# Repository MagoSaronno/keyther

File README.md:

# Keyther Keyboard
The Keyther Keyboard represents an attempt at perfecting the already great [Cantor Classic](https://github.com/diepala/cantor "The original project").  The name comes from the combination of the substantives **Keyboard** and **Ethernet**, due to the use of an RJ45 socket. 

*Special thanks to both [diepala](https://github.com/diepala "The Cantor Keyboard creator") and [daprice](https://github.com/daprice "The creator of the footprints libraries") for having paved the way for the creation of the Keyther Keyboard.*

### What changes from Cantor

1. The TRRS socket is replaced with the more secure RJ45 (Ethernet) to avoid *critical* integrity issues caused by accidental disconnection or hot-plugging.  Indeed, the Keyther Keyboard supports hot-plugging, as shown in this video:
 <p align="center"> 
   
</p>

2. The design introduces **hot-swappable** Kailh Choc **sockets** and **handedness by pin** (through the addition of a 10k resistor and an added line in the config.h file)
You won't have to desolder all 42 switches to change them and you will be able to connect the keyboard even through the right half.

3. The horizontal space between switches has been *increased*, accommodating larger hands **without** additional modifications to the overall PCB size (expept the space for the RJ45 socket).

### What does not change

The keyther keyboard keeps (*for the most part*) the original concepts that were at the origin of Cantor, which are the diodeless design and the use of an invertible PCB design, to ultimately avoid cuttable costs.

### Why RJ45 instead of USB-C or magnetic pogo pin sockets?

The main reasons to use RJ45 sockets are their easy soldering, their overall diffusion, and the widespread presence of premade cables of different kinds, like coiled, straight, and flat.

Additionally, the number of pins present on the socket allows the possible addition of two optional communication lines between PCBs for whatever use (namely pins 1 and 5).

# Be Aware
The Keyther Keyboard is designed to be used with ***STRAIGHT-THROUGH CABLES***, not the crossover ones.

***Always check the cable type before connecting the two halves***.

## Disclaimer
All the designs and files are provided "AS IS" without any warranty or support.

## Links Index

[Ordering Guide](docs/Ordering_Guide.md)

[Assembly Guide](docs/Assembling_Guide.md)

[Firmware Guide](https://qmk.fm/guide "The default guide for the Cantor Keyboard")

## Quick Guide

### Bill of Materials (BOM)
The required components needed to assemble the keyboard are the following:
| N. | Item                                                                                                                                        | Notes                                                                  |
|----|---------------------------------------------------------------------------------------------------------------------------------------------|------------------------------------------------------------------------|
| 2  | PCB board                                                                                                                                   |                                                                        |
| 2  | STM32F401CC BlackPill microcontrollers                                                                                                      | *on [AliExpress](https://it.aliexpress.com/item/1005005953179540.html?)* |
| 4  | 20 pin stripes                                                                                                                              | *usually included with the Blackpill*                                  |
| 42 | Kailh Choc ***v1*** switches                                                                                                                | *namely the Kailh PG1350*                                                |
| 42 | Kailh Choc hot-swap sockets                                                                                                                 |                                                                        |
| 42 | Kailh Choc ***v1*** compatible keycaps                                                                                                      |                                                                        |
| 2  | RJ45 sockets (RJHSE type, e.g., the [RJHSE-XM80](https://docs.rs-online.com/b456/A700000007566767.pdf "The technical drawing of the socket"))| *on [AliExpress](https://it.aliexpress.com/item/1005007661898327.html?)* |
| 1  | Straight-through Ethernet cable                                                                                                             | *flat ones seem to be more flexible and less annoying when using the keyboard*     |
| 1  | USB-C cable compatible with your computer                                                                                                   |                                                                        |

### Ordering the PCB
To order the PCB, you will need the Gerber files present in the [Release section](https://github.com/MagoSaronno/keyther/releases). Then, you can either compare the prices on [PCBShopper](https://pcbshopper.com/ "A price comparison site for printed PCBs") by choosing a dimension of 150x90mm or upload them directly to the PCB manufacturer's website of choice.

You can refer to the [Ordering Tutorial](docs/Ordering_Guide.md) page which provides a step-by-step guide on the ordering procedure.

> I personally prototyped my PCBs using JLCPCB, primarily due to lower prices. However, these may vary depending on your customs policies and regional shipping rates.

### Firmware
> It is preferable to flash and check the microcontroller for defects before assembling the keyboard.

The Keyther Keyboard uses the [QMK Firmware](https://qmk.fm/), specifically the same as the Cantor Keyboard. You can easily follow the [guide](https://qmk.fm/guide "The default guide for the Cantor Keyboard") on the QMK website to *customise* and *compile* the firmware.

To add **language-specific characters** (such as *accented* or *umlaut* vowels) you can follow this [additional guide](Language-Specific_Keymap.md).

Unfortunately, at this time, to add the handedness feature to your keyboard you will need to use the [QMK source](https://docs.qmk.fm/newbs "The guide to use the source"), and, before compiling, add to the cantor's config.h file the line:

`#define SPLIT_HAND_PIN B12`

### Enter Bootloader Mode
To flash the firmware onto the microcontroller you will need to set it in bootloader mode first:
- Press and hold the BOOT0 button.
- Press and release the NRST button.
- Release the BOOT0 button.

Now you will be able to flash the firmware and check if the microcontroller works properly.

> Once the first flash has been done successfully you will be able to enter bootloader mode just by plugging in one half of the keyboard **while** holding down the top-left or top-right (*whether it is the left or right keyboard half*).

### Assemble the keyboard
To assemble your Keyther Keyboard you will need a soldering iron and tin of your choice. You can also follow the [Assembly Guide](docs/Assembling_Guide.md).

### Printing the Keyther cases
To 3D print the cases to protect the bottom of your keyboard halves you will need to download the *.stl* files present in the [case folder](https://github.com/MagoSaronno/keyther/tree/main/case) of this repository and slice them with the appropriate software.

In case you wish to modify the designs, you can download the *.step* files in the [step folder](https://github.com/MagoSaronno/keyther/tree/main/case/step).
I've personally succeded in printing them using generic PLA with a layer height of 0.2mm and no supports.

## Feedback
You can fill out [this form](https://forms.gle/tCP48DNiQqiqbWwy6 "Leave here your much appreciated feedback") to let me know of any potential improvements or issues with the project. 

### Have fun!

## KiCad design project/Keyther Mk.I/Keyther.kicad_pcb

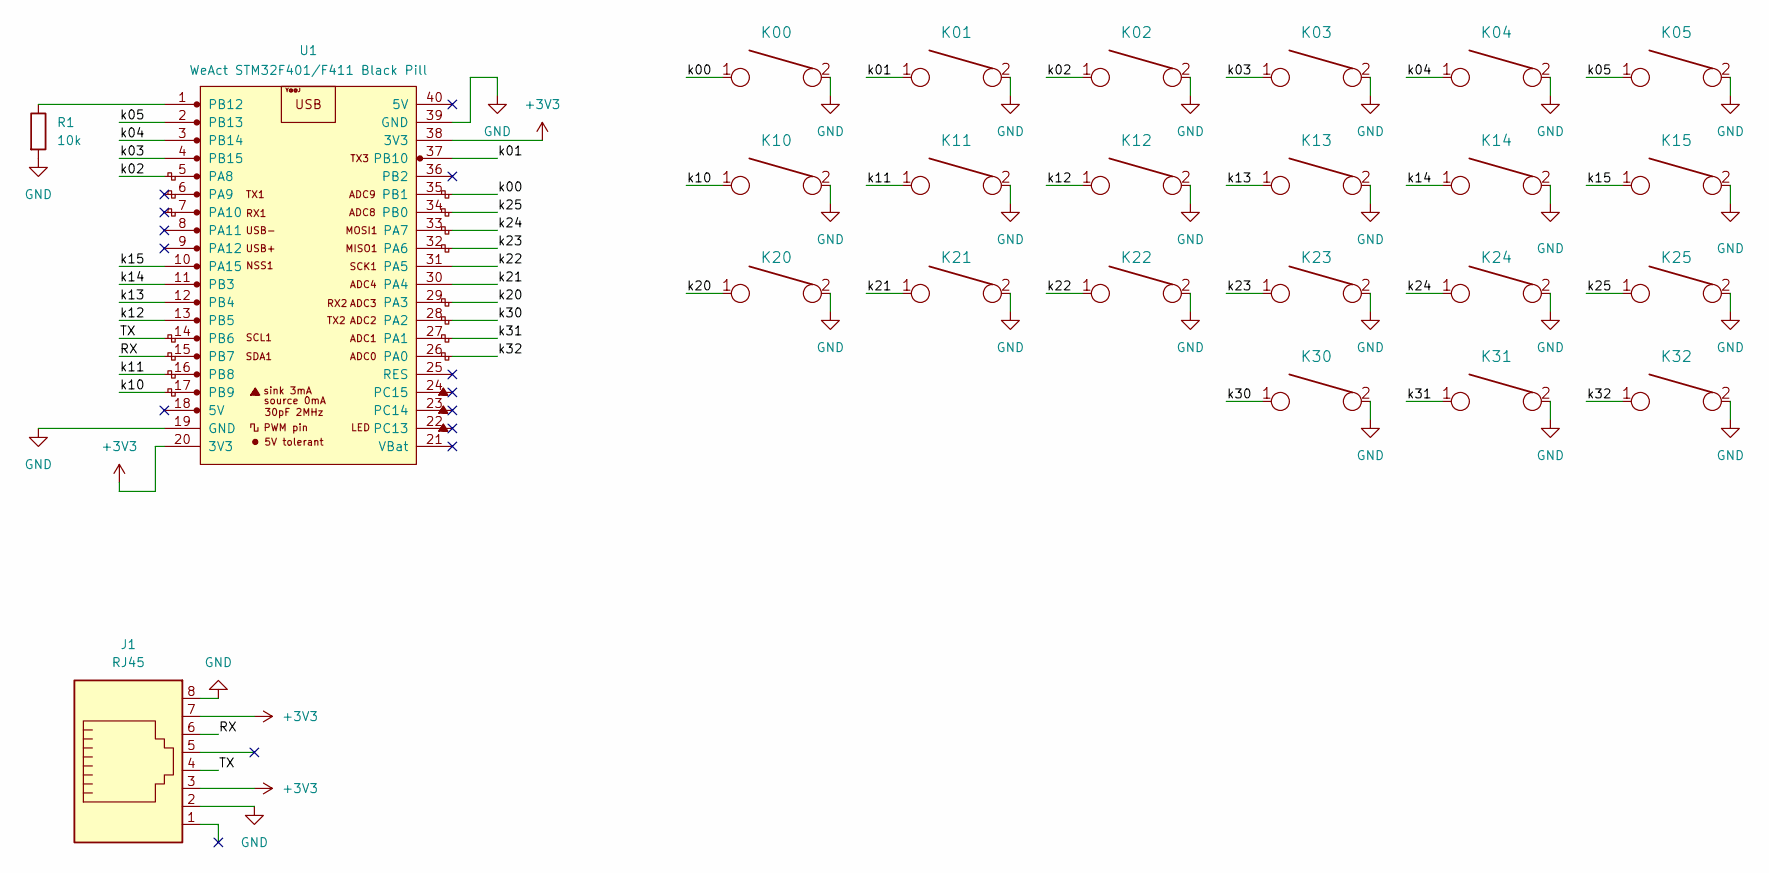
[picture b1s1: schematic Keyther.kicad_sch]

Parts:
J1: RJ45; RJ45_Amphenol_RJHSE5380
K00, K01, K02, K03, K04, K05, K10, K11, K12, K13, K14, K15, K20, K21, K22, K23, K24, K25, K30, K31, K32: KEYSW; Kailh_socket_PG1350_reversible
R1: 10k; R_Axial_DIN0207_L6.3mm_D2.5mm_P10.16mm_Horizontal
U1: YAAJ_WeAct_BlackPill_Part_Like; YAAJ_BlackPill_2

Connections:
+3V3: J1.3, J1.7, U1.20 (3V3), U1.38 (3V3)
/RX: J1.6, U1.15 (PB7)
/TX: J1.4, U1.14 (PB6)
/k00: K00.1, U1.35 (PB1)
/k01: K01.1, U1.37 (PB10)
/k02: K02.1, U1.5 (PA8)
/k03: K03.1, U1.4 (PB15)
/k04: K04.1, U1.3 (PB14)
/k05: K05.1, U1.2 (PB13)
/k10: K10.1, U1.17 (PB9)
/k11: K11.1, U1.16 (PB8)
/k12: K12.1, U1.13 (PB5)
/k13: K13.1, U1.12 (PB4)
/k14: K14.1, U1.11 (PB3)
/k15: K15.1, U1.10 (PA15)
/k20: K20.1, U1.29 (PA3)
/k21: K21.1, U1.30 (PA4)
/k22: K22.1, U1.31 (PA5)
/k23: K23.1, U1.32 (PA6)
/k24: K24.1, U1.33 (PA7)
/k25: K25.1, U1.34 (PB0)
/k30: K30.1, U1.28 (PA2)
/k31: K31.1, U1.27 (PA1)
/k32: K32.1, U1.26 (PA0)
GND: J1.2, J1.8, J1.SH, K00.2, K01.2, K02.2, K03.2, K04.2, K05.2, K10.2, K11.2, K12.2, K13.2, K14.2, K15.2, K20.2, K21.2, K22.2, K23.2, K24.2, K25.2, K30.2, K31.2, K32.2, R1.2, U1.19 (GND), U1.39 (GND)
unnamed: R1.1, U1.1 (PB12)

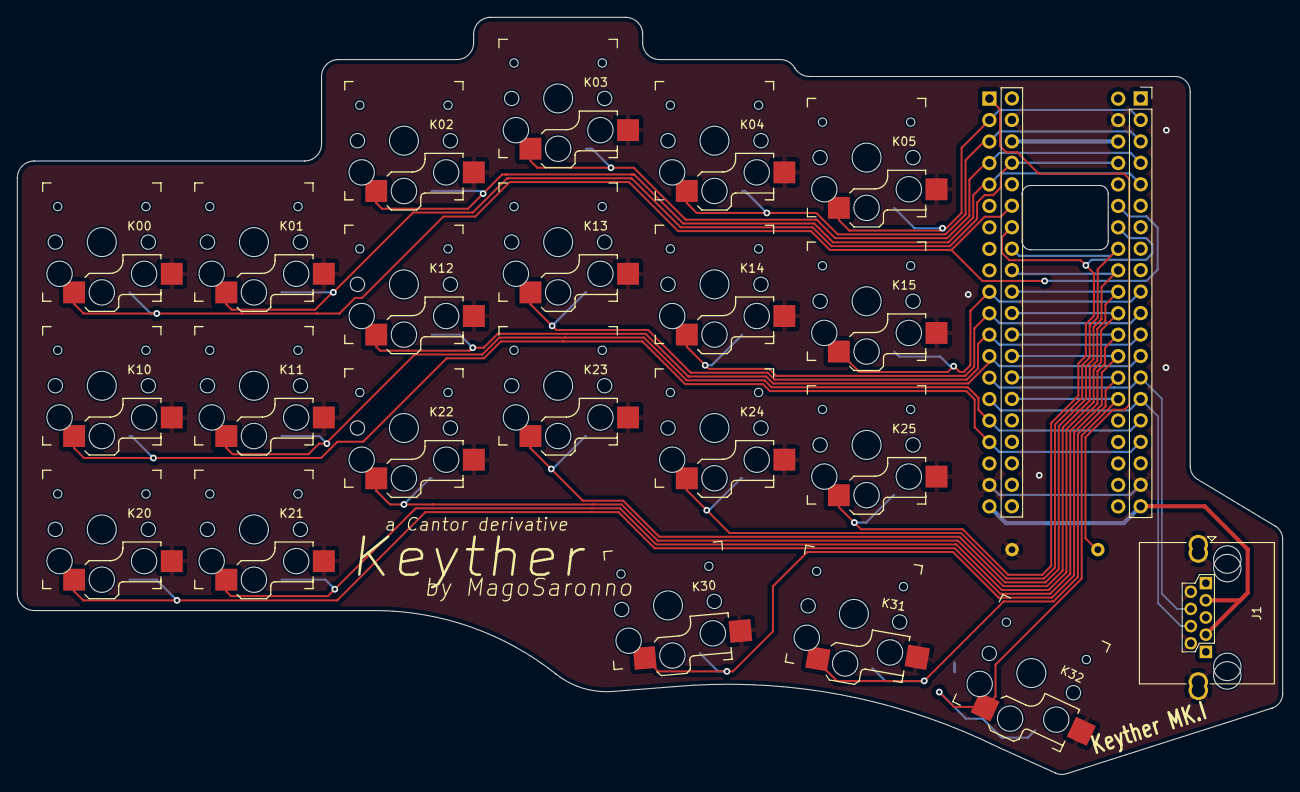
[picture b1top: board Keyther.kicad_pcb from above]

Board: 2 copper layers, 149.7 x 89.6 mm, 24 parts (1 on the bottom side), 26 nets.

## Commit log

2025-12-28 Create LICENSE
2025-12-28 First README.md
2025-12-31 Update Assembly
2026-01-06 Added 3D printable case files and step for modding
2026-01-06 Updating images
2026-01-06 Added updated images
2026-01-07 Fixed README.md
2026-01-07 Added updated version project files
2026-01-07 Updated Assembly_Guide.md to accomodate Mk. I design
